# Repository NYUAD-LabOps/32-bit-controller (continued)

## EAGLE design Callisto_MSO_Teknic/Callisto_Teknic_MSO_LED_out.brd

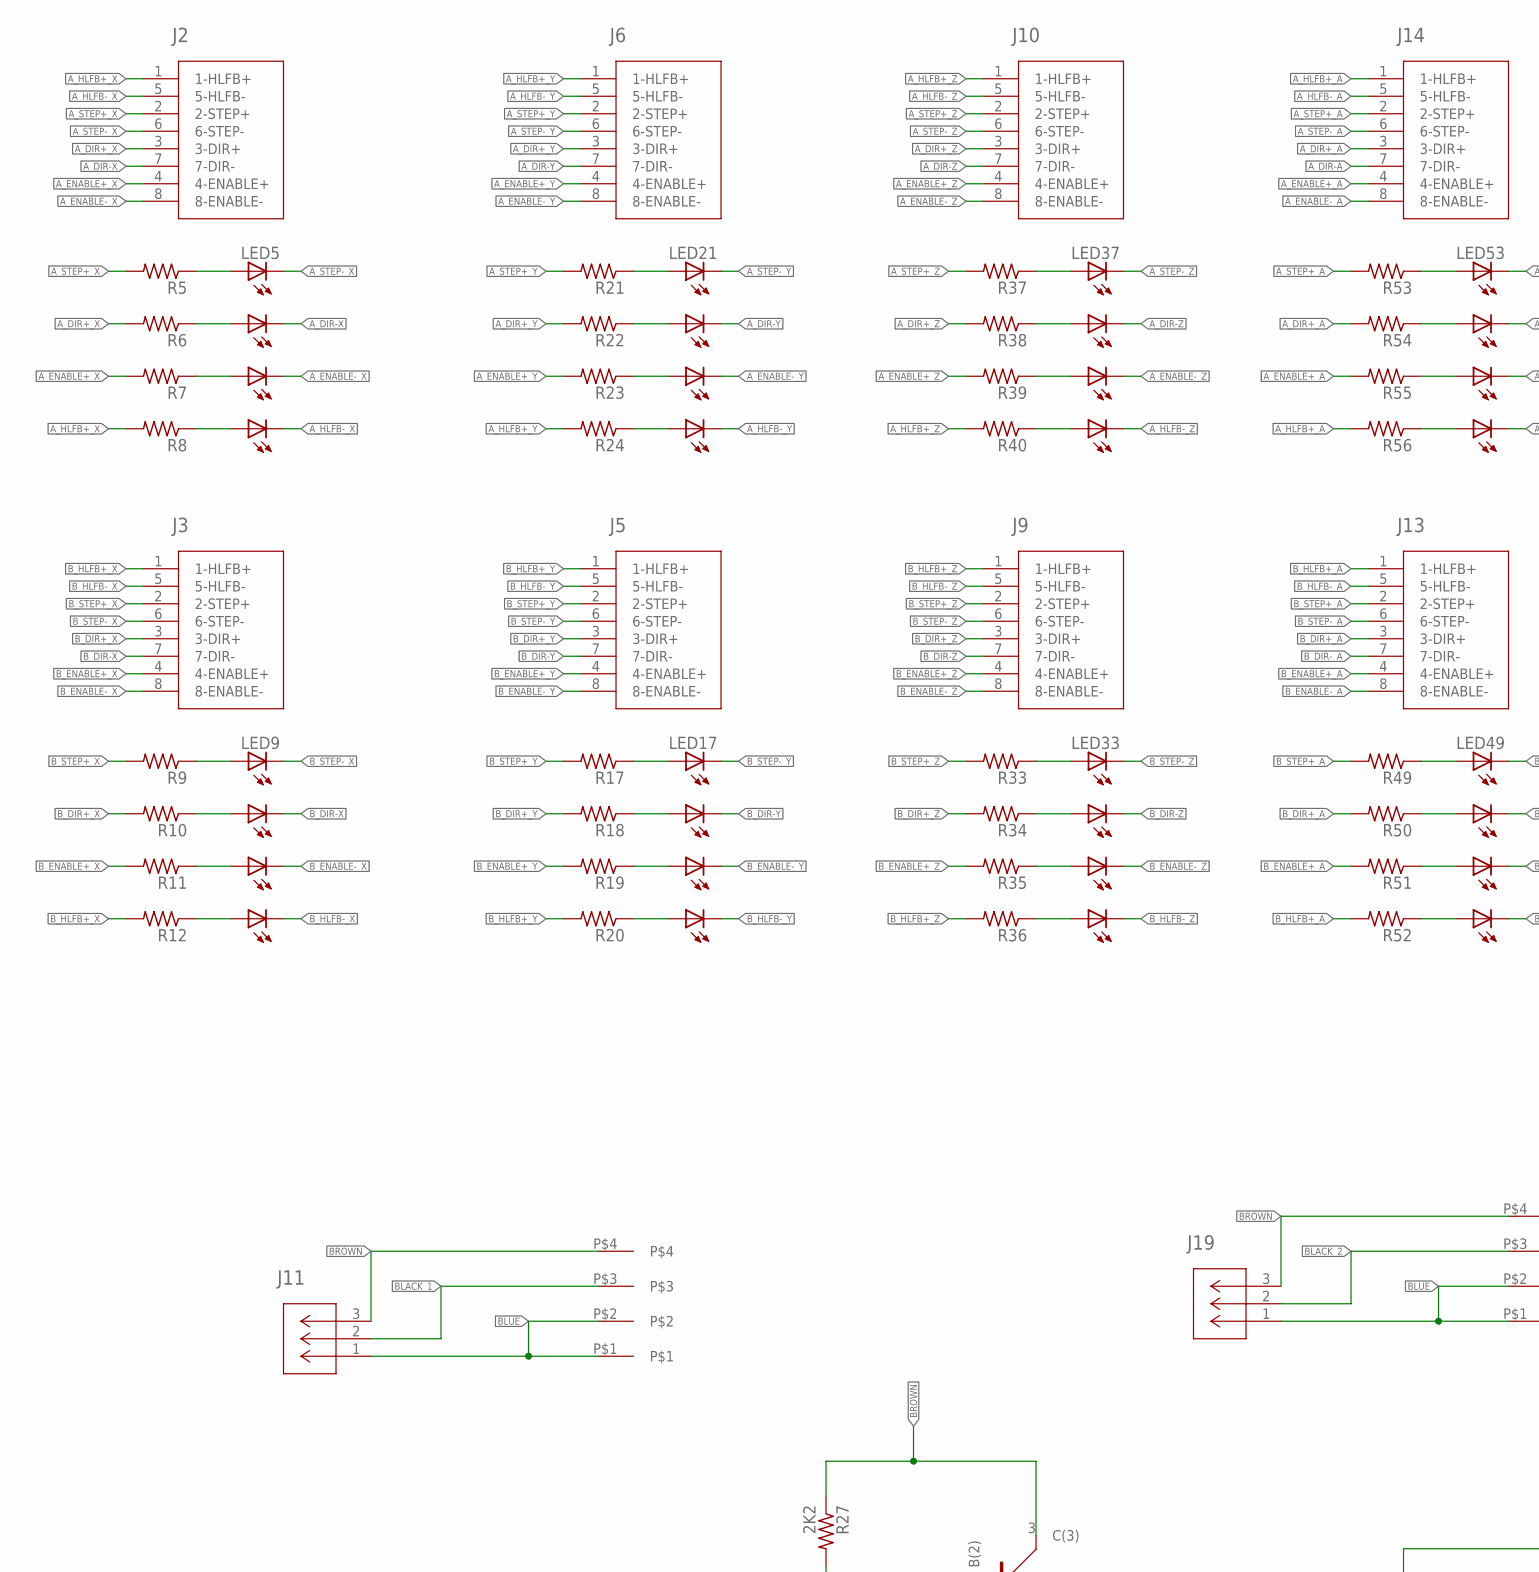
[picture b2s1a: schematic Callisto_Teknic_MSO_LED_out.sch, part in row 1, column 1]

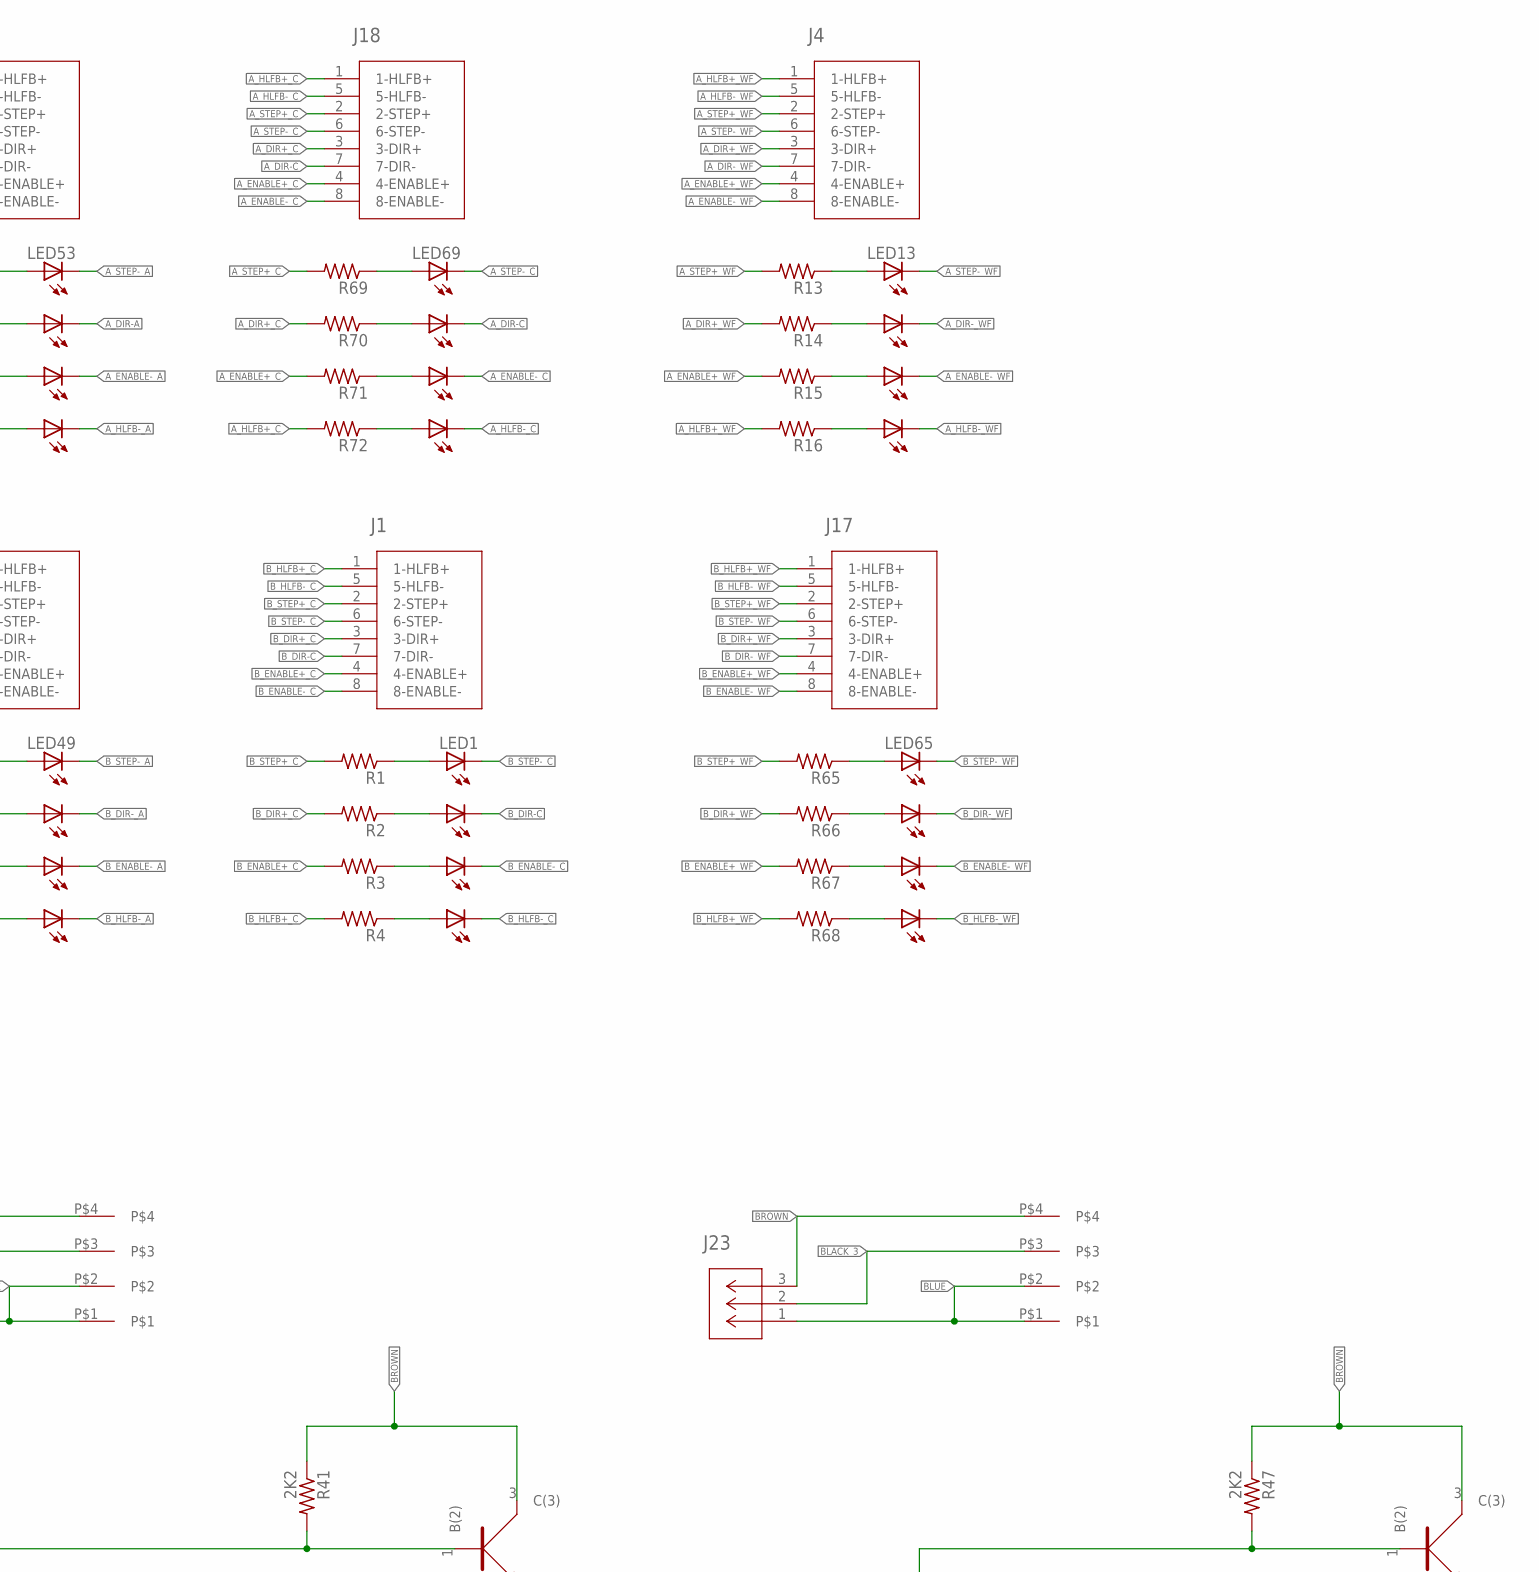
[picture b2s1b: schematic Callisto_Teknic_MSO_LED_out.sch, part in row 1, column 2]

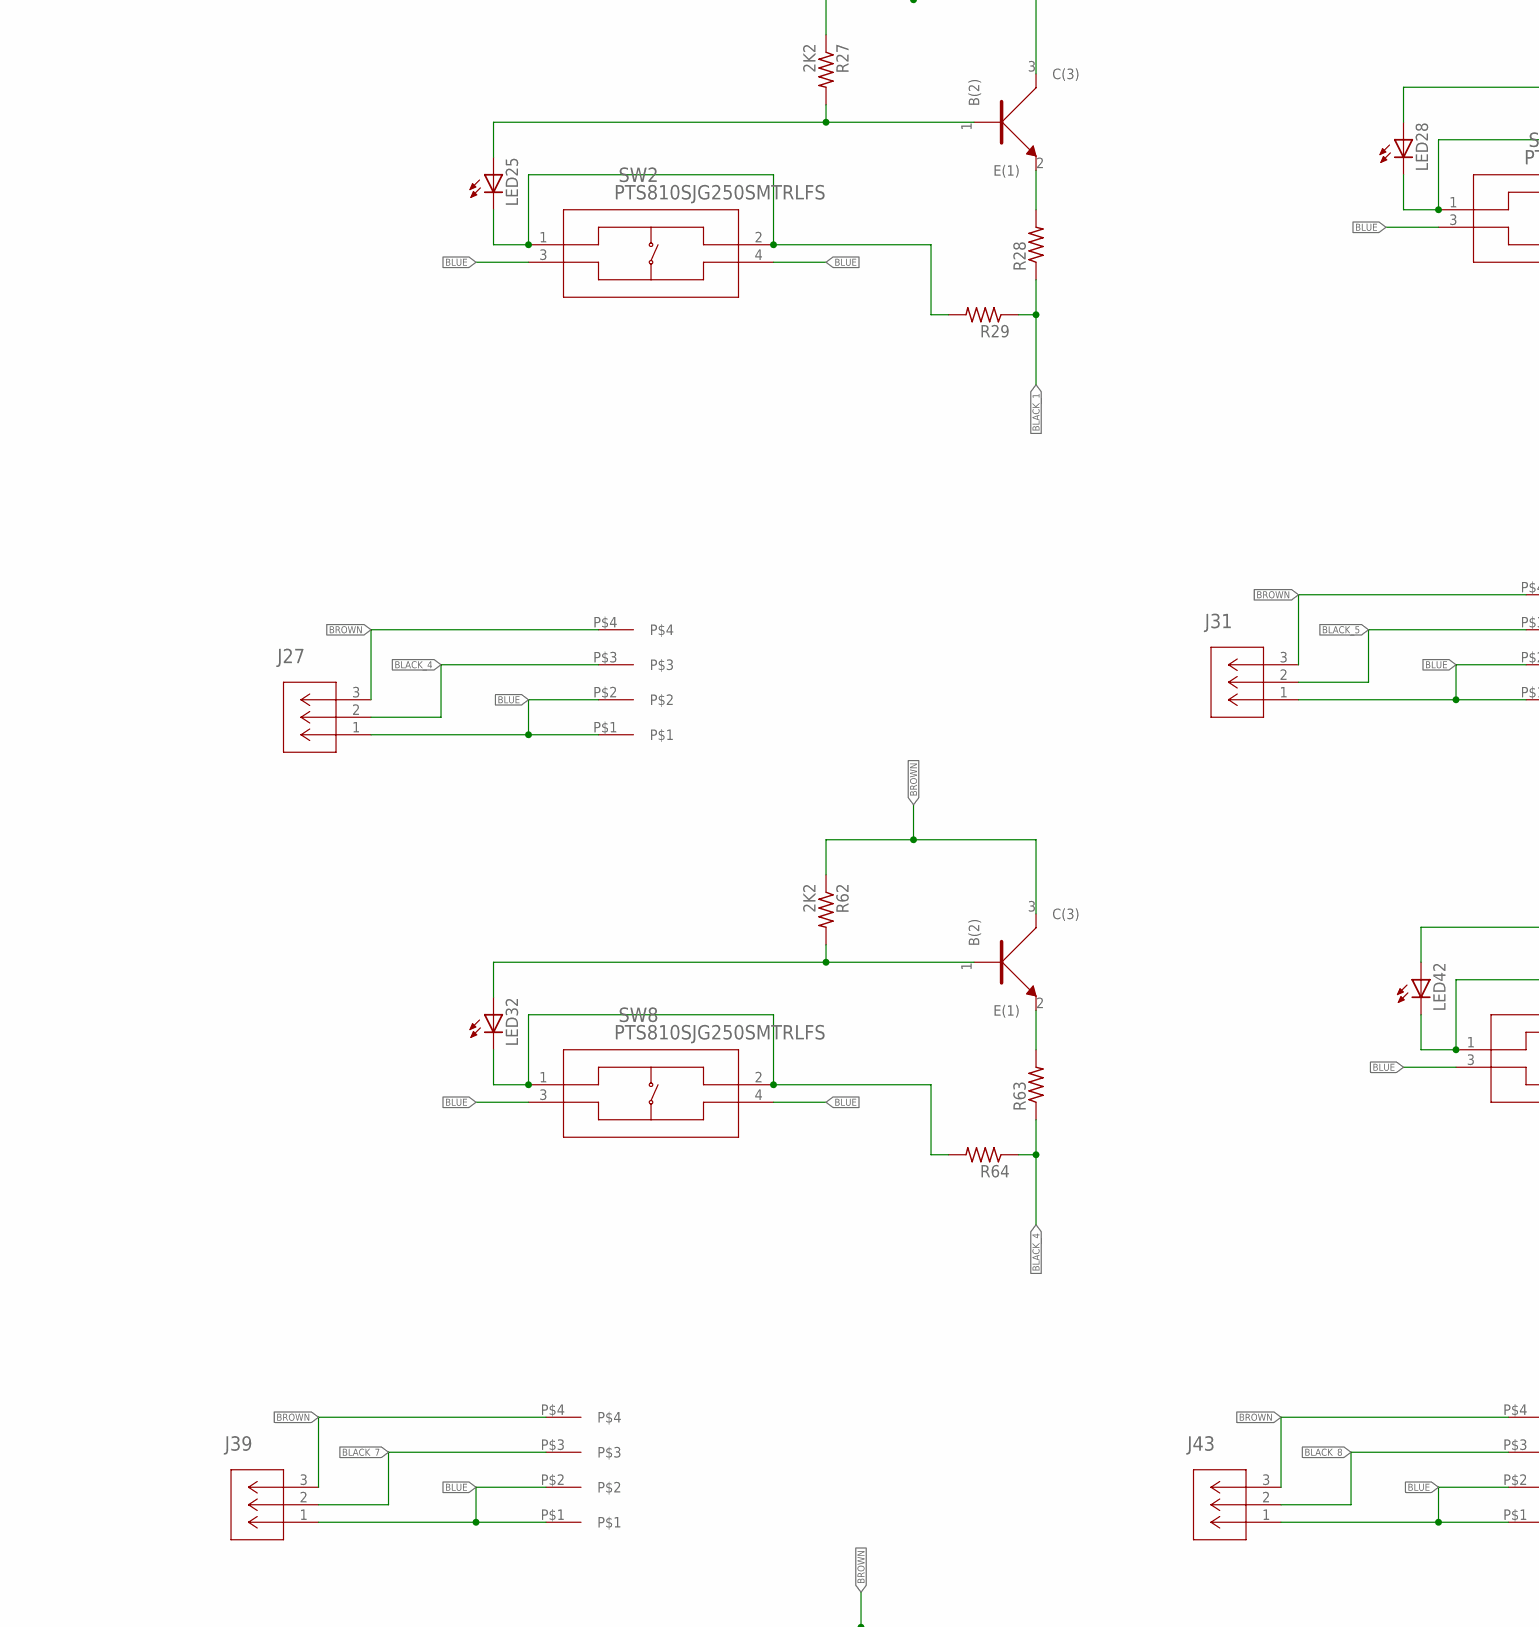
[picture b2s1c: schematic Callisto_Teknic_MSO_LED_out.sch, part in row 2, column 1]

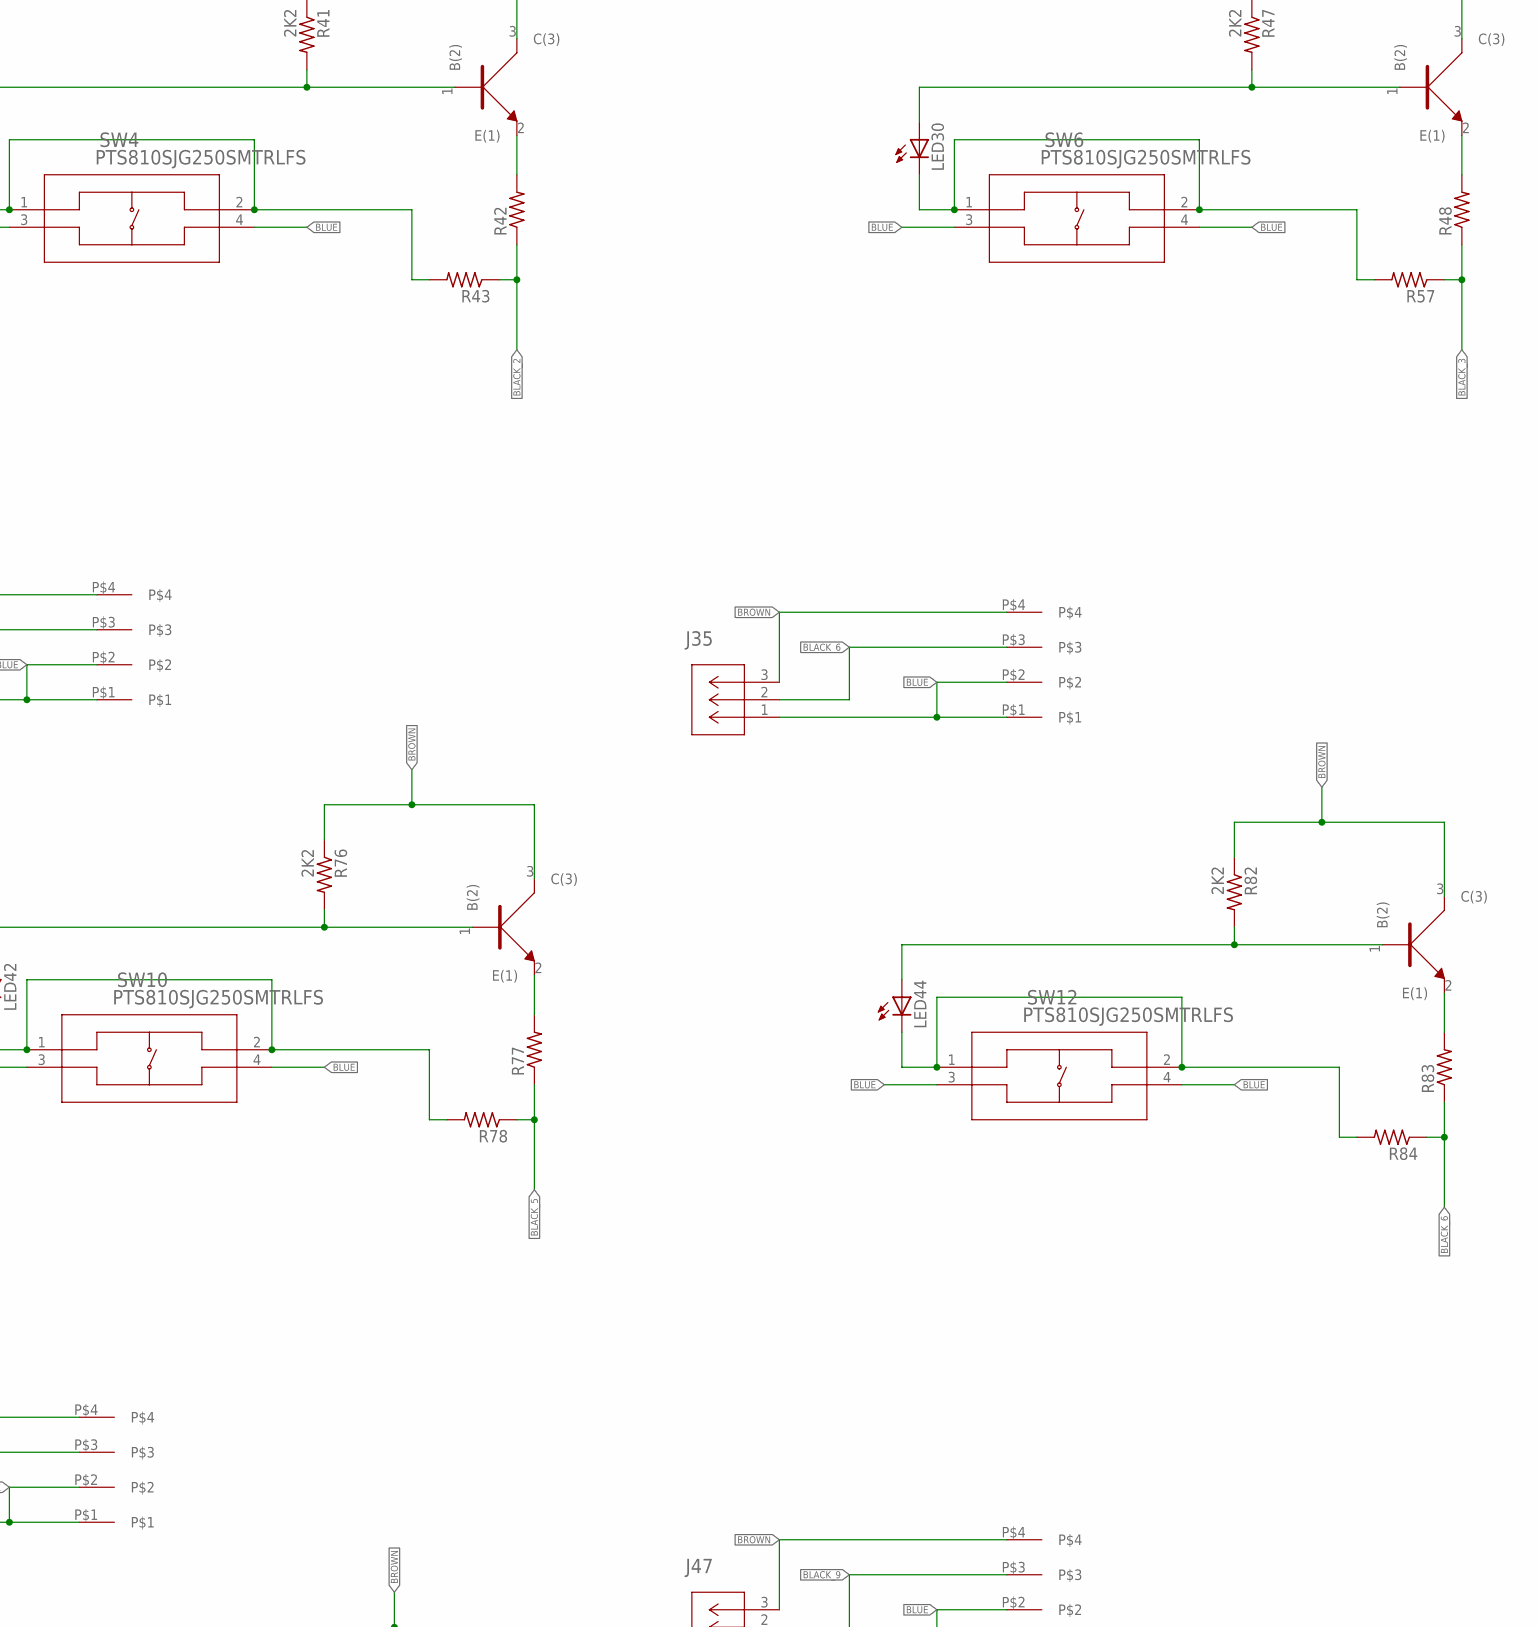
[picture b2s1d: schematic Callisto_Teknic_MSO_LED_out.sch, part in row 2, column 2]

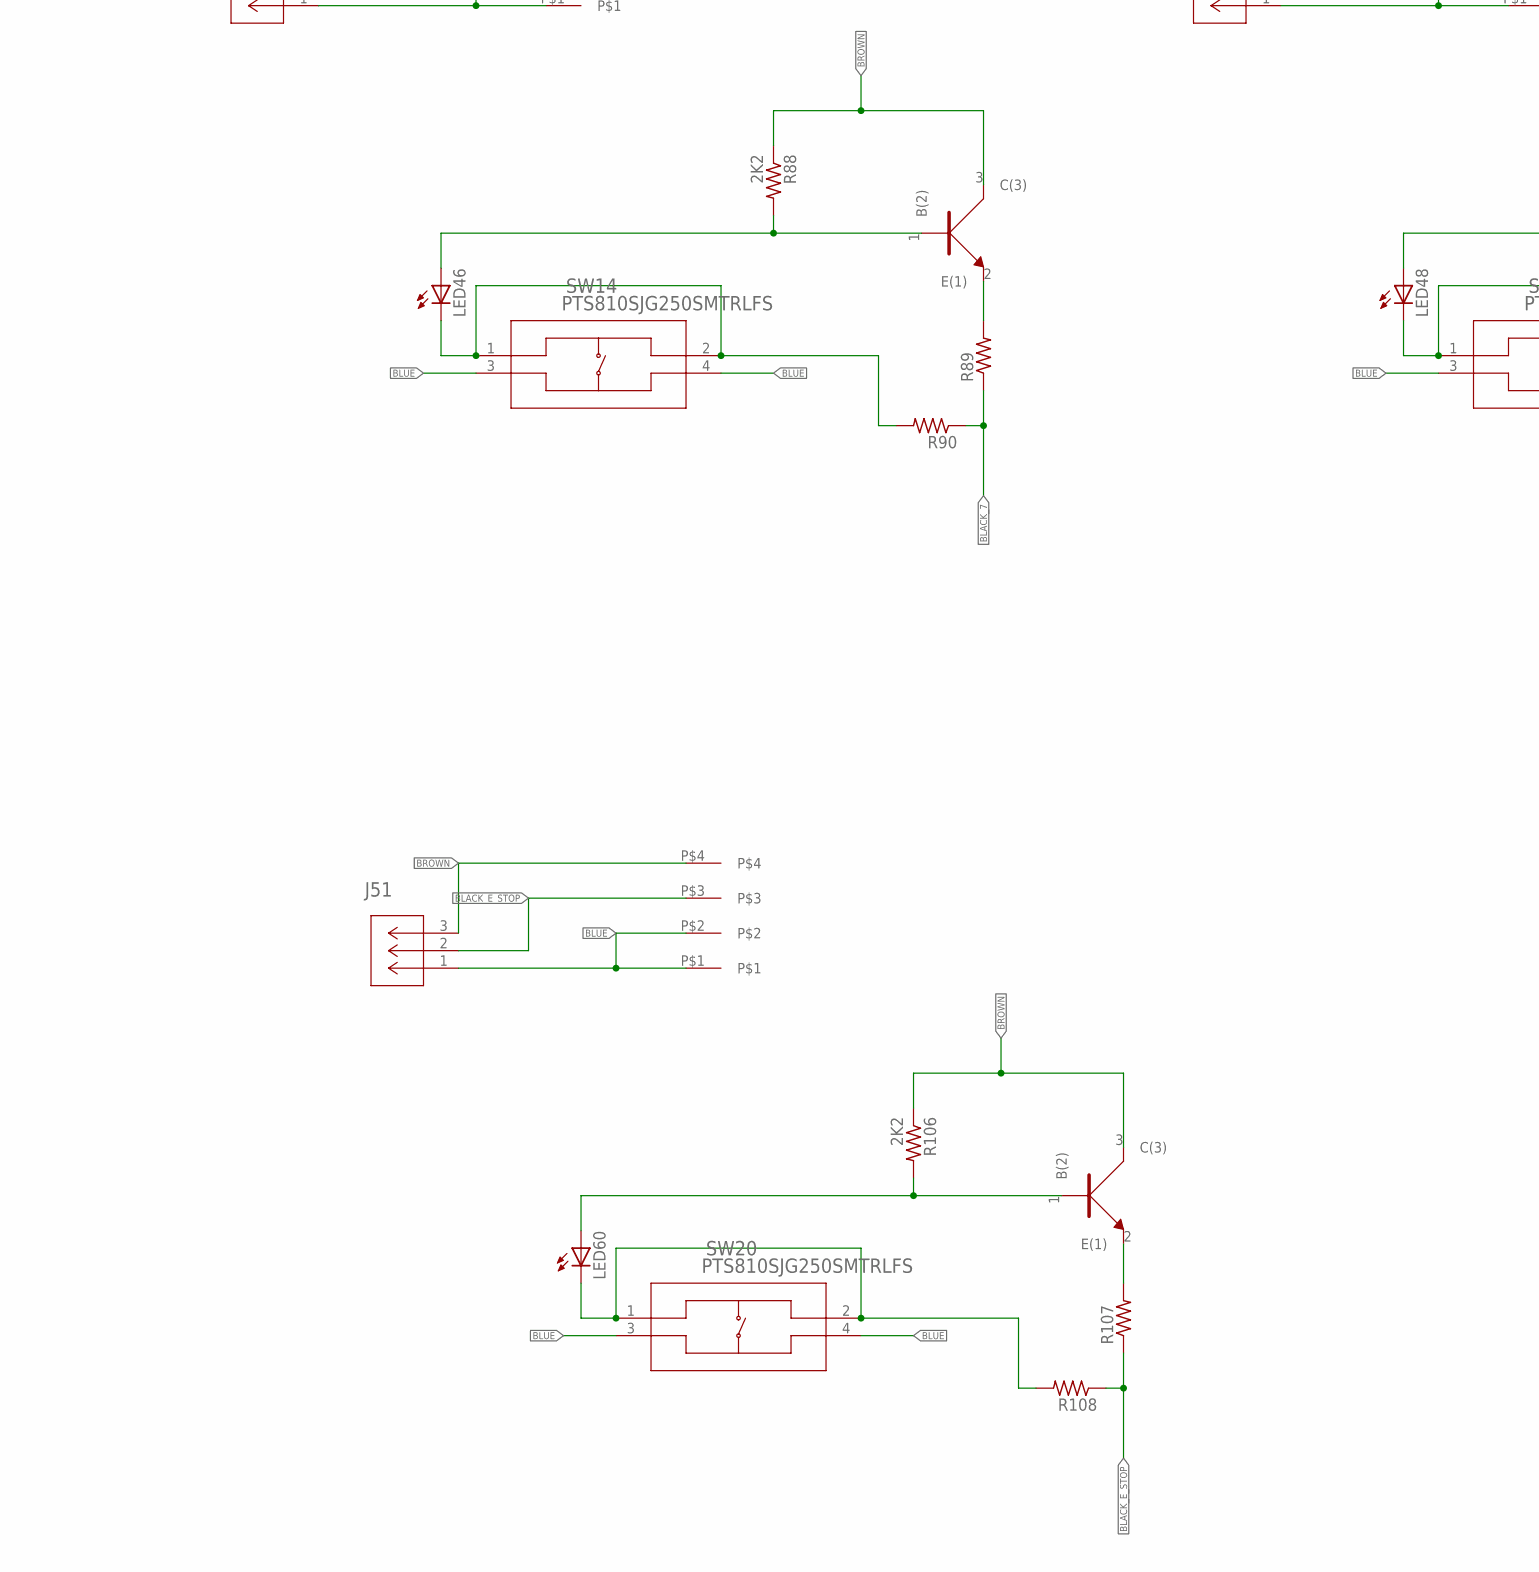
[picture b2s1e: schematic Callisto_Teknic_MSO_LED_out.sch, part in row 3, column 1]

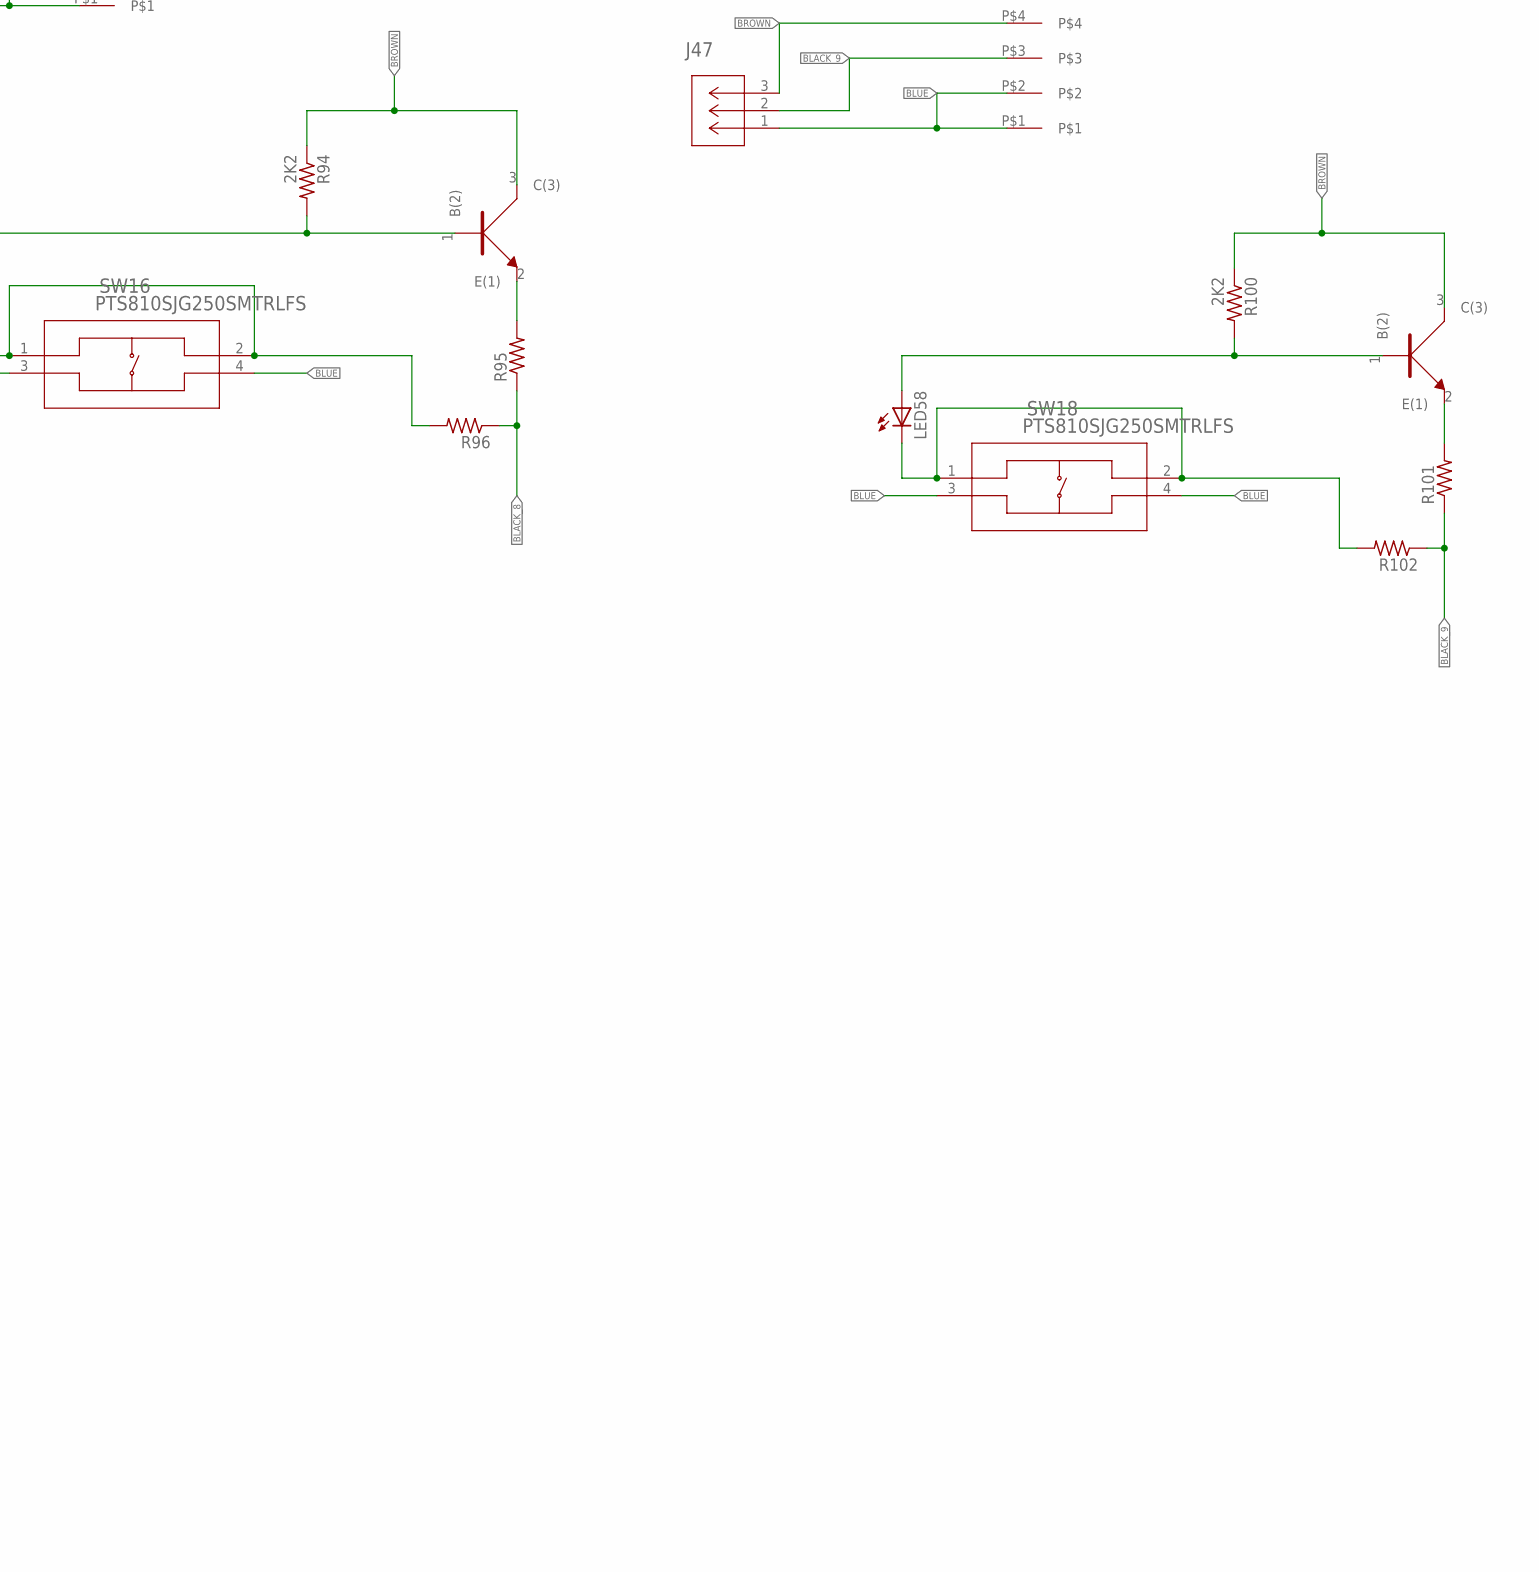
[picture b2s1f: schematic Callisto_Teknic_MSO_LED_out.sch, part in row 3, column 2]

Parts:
J1, J2, J3, J4, J5, J6, J9, J10, J13, J14, J17, J18: TEKNIC_MOTOR_SD_8PIN; CON_39281083
J11, J19, J23, J27, J31, J35, J39, J43, J47, J51: CONN_530470310_PICOBLADE_X_3; CON_530470310_MOL
J12, J20, J24, J28, J32, J36, J40, J44, J48, J52: 4-pos; 1X4_3.81MM_PITCH
LED1, LED2, LED3, LED4, LED5, LED6, LED7, LED8, LED9, LED10, LED11, LED12, LED13, LED14, LED15, LED16, LED17, LED18, LED19, LED20, LED21, LED22, LED23, LED24, LED25, LED28, LED30, LED32, LED33, LED34, LED35, LED36, LED37, LED38, LED39, LED40, LED42, LED44, LED46, LED48, LED49, LED50, LED51, LED52, LED53, LED54, LED55, LED56, LED58, LED60, LED65, LED66, LED67, LED68, LED69, LED70, LED71, LED72: Green; 0805
R1, R2, R3, R4, R5, R6, R7, R8, R9, R10, R11, R12, R13, R14, R15, R16, R17, R18, R19, R20, R21, R22, R23, R24, R33, R34, R35, R36, R37, R38, R39, R40, R49, R50, R51, R52, R53, R54, R55, R56, R65, R66, R67, R68, R69, R70, R71, R72: R_0805; 0805
R27, R41, R47, R62, R76, R82, R88, R94, R100, R106: 2K2; 0402
R28, R29, R42, R43, R48, R57, R63, R64, R77, R78, R83, R84, R89, R90, R95, R96, R101, R102, R107, R108: R_0402; 0402
SW2, SW4, SW6, SW8, SW10, SW12, SW14, SW16, SW18, SW20: PTS810SJG250SMTRLFS; PTS810
U1, U3, U5, U7, U9, U11, U13, U15, U17, U20: NPN; SOT323

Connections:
A_DIR+_A: J14.3 (3-DIR+), R54.2
A_DIR+_C: J18.3 (3-DIR+), R70.2
A_DIR+_WF: J4.3 (3-DIR+), R14.2
A_DIR+_X: J2.3 (3-DIR+), R6.2
A_DIR+_Y: J6.3 (3-DIR+), R22.2
A_DIR+_Z: J10.3 (3-DIR+), R38.2
A_DIR-A: J14.7 (7-DIR-), LED54.2 (C)
A_DIR-C: J18.7 (7-DIR-), LED70.2 (C)
A_DIR-X: J2.7 (7-DIR-), LED6.2 (C)
A_DIR-Y: J6.7 (7-DIR-), LED22.2 (C)
A_DIR-Z: J10.7 (7-DIR-), LED38.2 (C)
A_DIR-_WF: J4.7 (7-DIR-), LED14.2 (C)
A_ENABLE+_A: J14.4 (4-ENABLE+), R55.2
A_ENABLE+_C: J18.4 (4-ENABLE+), R71.2
A_ENABLE+_WF: J4.4 (4-ENABLE+), R15.2
A_ENABLE+_X: J2.4 (4-ENABLE+), R7.2
A_ENABLE+_Y: J6.4 (4-ENABLE+), R23.2
A_ENABLE+_Z: J10.4 (4-ENABLE+), R39.2
A_ENABLE-_A: J14.8 (8-ENABLE-), LED55.2 (C)
A_ENABLE-_C: J18.8 (8-ENABLE-), LED71.2 (C)
A_ENABLE-_WF: J4.8 (8-ENABLE-), LED15.2 (C)
A_ENABLE-_X: J2.8 (8-ENABLE-), LED7.2 (C)
A_ENABLE-_Y: J6.8 (8-ENABLE-), LED23.2 (C)
A_ENABLE-_Z: J10.8 (8-ENABLE-), LED39.2 (C)
A_HLFB+_A: J14.1 (1-HLFB+), R56.2
A_HLFB+_C: J18.1 (1-HLFB+), R72.2
A_HLFB+_WF: J4.1 (1-HLFB+), R16.2
A_HLFB+_X: J2.1 (1-HLFB+), R8.2
A_HLFB+_Y: J6.1 (1-HLFB+), R24.2
A_HLFB+_Z: J10.1 (1-HLFB+), R40.2
A_HLFB-_A: J14.5 (5-HLFB-), LED56.2 (C)
A_HLFB-_C: J18.5 (5-HLFB-), LED72.2 (C)
A_HLFB-_WF: J4.5 (5-HLFB-), LED16.2 (C)
A_HLFB-_X: J2.5 (5-HLFB-), LED8.2 (C)
A_HLFB-_Y: J6.5 (5-HLFB-), LED24.2 (C)
A_HLFB-_Z: J10.5 (5-HLFB-), LED40.2 (C)
A_STEP+_A: J14.2 (2-STEP+), R53.2
A_STEP+_C: J18.2 (2-STEP+), R69.2
A_STEP+_WF: J4.2 (2-STEP+), R13.2
A_STEP+_X: J2.2 (2-STEP+), R5.2
A_STEP+_Y: J6.2 (2-STEP+), R21.2
A_STEP+_Z: J10.2 (2-STEP+), R37.2
A_STEP-_A: J14.6 (6-STEP-), LED53.2 (C)
A_STEP-_C: J18.6 (6-STEP-), LED69.2 (C)
A_STEP-_WF: J4.6 (6-STEP-), LED13.2 (C)
A_STEP-_X: J2.6 (6-STEP-), LED5.2 (C)
A_STEP-_Y: J6.6 (6-STEP-), LED21.2 (C)
A_STEP-_Z: J10.6 (6-STEP-), LED37.2 (C)
BLACK_1: J11.2, J12.P$3, R28.P$1 (1), R29.P$1 (1)
BLACK_2: J19.2, J20.P$3, R42.P$1 (1), R43.P$1 (1)
BLACK_3: J23.2, J24.P$3, R48.P$1 (1), R57.P$1 (1)
BLACK_4: J27.2, J28.P$3, R63.P$1 (1), R64.P$1 (1)
BLACK_5: J31.2, J32.P$3, R77.P$1 (1), R78.P$1 (1)
BLACK_6: J35.2, J36.P$3, R83.P$1 (1), R84.P$1 (1)
BLACK_7: J39.2, J40.P$3, R89.P$1 (1), R90.P$1 (1)
BLACK_8: J43.2, J44.P$3, R95.P$1 (1), R96.P$1 (1)
BLACK_9: J47.2, J48.P$3, R101.P$1 (1), R102.P$1 (1)
BLACK_E_STOP: J51.2, J52.P$3, R107.P$1 (1), R108.P$1 (1)
BLUE: J11.1, J12.P$1, J12.P$2, J19.1, J20.P$1, J20.P$2, J23.1, J24.P$1, J24.P$2, J27.1, J28.P$1, J28.P$2, J31.1, J32.P$1, J32.P$2, J35.1, J36.P$1, J36.P$2, J39.1, J40.P$1, J40.P$2, J43.1, J44.P$1, J44.P$2, J47.1, J48.P$1, J48.P$2, J51.1, J52.P$1, J52.P$2, SW2.3, SW2.4, SW4.3, SW4.4, SW6.3, SW6.4, SW8.3, SW8.4, SW10.3, SW10.4, SW12.3, SW12.4, SW14.3, SW14.4, SW16.3, SW16.4, SW18.3, SW18.4, SW20.3, SW20.4
BROWN: J11.3, J12.P$4, J19.3, J20.P$4, J23.3, J24.P$4, J27.3, J28.P$4, J31.3, J32.P$4, J35.3, J36.P$4, J39.3, J40.P$4, J43.3, J44.P$4, J47.3, J48.P$4, J51.3, J52.P$4, R27.P$1 (1), R41.P$1 (1), R47.P$1 (1), R62.P$1 (1), R76.P$1 (1), R82.P$1 (1), R88.P$1 (1), R94.P$1 (1), R100.P$1 (1), R106.P$1 (1), U1.3 (C(3)), U3.3 (C(3)), U5.3 (C(3)), U7.3 (C(3)), U9.3 (C(3)), U11.3 (C(3)), U13.3 (C(3)), U15.3 (C(3)), U17.3 (C(3)), U20.3 (C(3))
B_DIR+_A: J13.3 (3-DIR+), R50.2
B_DIR+_C: J1.3 (3-DIR+), R2.2
B_DIR+_WF: J17.3 (3-DIR+), R66.2
B_DIR+_X: J3.3 (3-DIR+), R10.2
B_DIR+_Y: J5.3 (3-DIR+), R18.2
B_DIR+_Z: J9.3 (3-DIR+), R34.2
B_DIR-C: J1.7 (7-DIR-), LED2.2 (C)
B_DIR-X: J3.7 (7-DIR-), LED10.2 (C)
B_DIR-Y: J5.7 (7-DIR-), LED18.2 (C)
B_DIR-Z: J9.7 (7-DIR-), LED34.2 (C)
B_DIR-_A: J13.7 (7-DIR-), LED50.2 (C)
B_DIR-_WF: J17.7 (7-DIR-), LED66.2 (C)
B_ENABLE+_A: J13.4 (4-ENABLE+), R51.2
B_ENABLE+_C: J1.4 (4-ENABLE+), R3.2
B_ENABLE+_WF: J17.4 (4-ENABLE+), R67.2
B_ENABLE+_X: J3.4 (4-ENABLE+), R11.2
B_ENABLE+_Y: J5.4 (4-ENABLE+), R19.2
B_ENABLE+_Z: J9.4 (4-ENABLE+), R35.2
B_ENABLE-_A: J13.8 (8-ENABLE-), LED51.2 (C)
B_ENABLE-_C: J1.8 (8-ENABLE-), LED3.2 (C)
B_ENABLE-_WF: J17.8 (8-ENABLE-), LED67.2 (C)
B_ENABLE-_X: J3.8 (8-ENABLE-), LED11.2 (C)
B_ENABLE-_Y: J5.8 (8-ENABLE-), LED19.2 (C)
B_ENABLE-_Z: J9.8 (8-ENABLE-), LED35.2 (C)
B_HLFB+_A: J13.1 (1-HLFB+), R52.2
B_HLFB+_C: J1.1 (1-HLFB+), R4.2
B_HLFB+_WF: J17.1 (1-HLFB+), R68.2
B_HLFB+_X: J3.1 (1-HLFB+), R12.2
B_HLFB+_Y: J5.1 (1-HLFB+), R20.2
B_HLFB+_Z: J9.1 (1-HLFB+), R36.2
B_HLFB-_A: J13.5 (5-HLFB-), LED52.2 (C)
B_HLFB-_C: J1.5 (5-HLFB-), LED4.2 (C)
B_HLFB-_WF: J17.5 (5-HLFB-), LED68.2 (C)
B_HLFB-_X: J3.5 (5-HLFB-), LED12.2 (C)
B_HLFB-_Y: J5.5 (5-HLFB-), LED20.2 (C)
B_HLFB-_Z: J9.5 (5-HLFB-), LED36.2 (C)
B_STEP+_A: J13.2 (2-STEP+), R49.2
B_STEP+_C: J1.2 (2-STEP+), R1.2
B_STEP+_WF: J17.2 (2-STEP+), R65.2
B_STEP+_X: J3.2 (2-STEP+), R9.2
B_STEP+_Y: J5.2 (2-STEP+), R17.2
B_STEP+_Z: J9.2 (2-STEP+), R33.2
B_STEP-_A: J13.6 (6-STEP-), LED49.2 (C)
B_STEP-_C: J1.6 (6-STEP-), LED1.2 (C)
B_STEP-_WF: J17.6 (6-STEP-), LED65.2 (C)
B_STEP-_X: J3.6 (6-STEP-), LED9.2 (C)
B_STEP-_Y: J5.6 (6-STEP-), LED17.2 (C)
B_STEP-_Z: J9.6 (6-STEP-), LED33.2 (C)
unnamed: LED1.1 (A), R1.1
unnamed: LED2.1 (A), R2.1
unnamed: LED3.1 (A), R3.1
unnamed: LED4.1 (A), R4.1
unnamed: LED5.1 (A), R5.1
unnamed: LED6.1 (A), R6.1
unnamed: LED7.1 (A), R7.1
unnamed: LED8.1 (A), R8.1
unnamed: LED9.1 (A), R9.1
unnamed: LED10.1 (A), R10.1
unnamed: LED11.1 (A), R11.1
unnamed: LED12.1 (A), R12.1
unnamed: LED13.1 (A), R13.1
unnamed: LED14.1 (A), R14.1
unnamed: LED15.1 (A), R15.1
unnamed: LED16.1 (A), R16.1
unnamed: LED17.1 (A), R17.1
unnamed: LED18.1 (A), R18.1
unnamed: LED19.1 (A), R19.1
unnamed: LED20.1 (A), R20.1
unnamed: LED21.1 (A), R21.1
unnamed: LED22.1 (A), R22.1
unnamed: LED23.1 (A), R23.1
unnamed: LED24.1 (A), R24.1
unnamed: LED25.1 (A), R27.P$2 (2), U1.1 (B(2))
unnamed: LED25.2 (C), R29.P$2 (2), SW2.1, SW2.2
unnamed: R28.P$2 (2), U1.2 (E(1))
unnamed: LED33.1 (A), R33.1
unnamed: LED34.1 (A), R34.1
unnamed: LED35.1 (A), R35.1
unnamed: LED36.1 (A), R36.1
unnamed: LED37.1 (A), R37.1
unnamed: LED38.1 (A), R38.1
unnamed: LED39.1 (A), R39.1
unnamed: LED40.1 (A), R40.1
unnamed: LED28.1 (A), R41.P$2 (2), U3.1 (B(2))
unnamed: LED28.2 (C), R43.P$2 (2), SW4.1, SW4.2
unnamed: R42.P$2 (2), U3.2 (E(1))
unnamed: LED30.1 (A), R47.P$2 (2), U5.1 (B(2))
unnamed: LED49.1 (A), R49.1
unnamed: LED50.1 (A), R50.1
unnamed: LED51.1 (A), R51.1
unnamed: LED52.1 (A), R52.1
unnamed: LED53.1 (A), R53.1
unnamed: LED54.1 (A), R54.1
unnamed: LED55.1 (A), R55.1
unnamed: LED56.1 (A), R56.1
unnamed: LED30.2 (C), R57.P$2 (2), SW6.1, SW6.2
unnamed: R48.P$2 (2), U5.2 (E(1))
unnamed: LED32.1 (A), R62.P$2 (2), U7.1 (B(2))
unnamed: LED32.2 (C), R64.P$2 (2), SW8.1, SW8.2
unnamed: R63.P$2 (2), U7.2 (E(1))
unnamed: LED65.1 (A), R65.1
unnamed: LED66.1 (A), R66.1
unnamed: LED67.1 (A), R67.1
unnamed: LED68.1 (A), R68.1
unnamed: LED69.1 (A), R69.1
unnamed: LED70.1 (A), R70.1
unnamed: LED71.1 (A), R71.1
unnamed: LED72.1 (A), R72.1
unnamed: LED42.1 (A), R76.P$2 (2), U9.1 (B(2))
unnamed: LED42.2 (C), R78.P$2 (2), SW10.1, SW10.2
unnamed: R77.P$2 (2), U9.2 (E(1))
unnamed: LED44.1 (A), R82.P$2 (2), U11.1 (B(2))
unnamed: LED44.2 (C), R84.P$2 (2), SW12.1, SW12.2
unnamed: R83.P$2 (2), U11.2 (E(1))
unnamed: LED46.1 (A), R88.P$2 (2), U13.1 (B(2))
unnamed: LED46.2 (C), R90.P$2 (2), SW14.1, SW14.2
unnamed: R89.P$2 (2), U13.2 (E(1))
unnamed: LED48.1 (A), R94.P$2 (2), U15.1 (B(2))
unnamed: LED48.2 (C), R96.P$2 (2), SW16.1, SW16.2
unnamed: R95.P$2 (2), U15.2 (E(1))
unnamed: LED58.1 (A), R100.P$2 (2), U17.1 (B(2))
unnamed: LED58.2 (C), R102.P$2 (2), SW18.1, SW18.2
unnamed: R101.P$2 (2), U17.2 (E(1))
unnamed: LED60.1 (A), R106.P$2 (2), U20.1 (B(2))
unnamed: LED60.2 (C), R108.P$2 (2), SW20.1, SW20.2
unnamed: R107.P$2 (2), U20.2 (E(1))

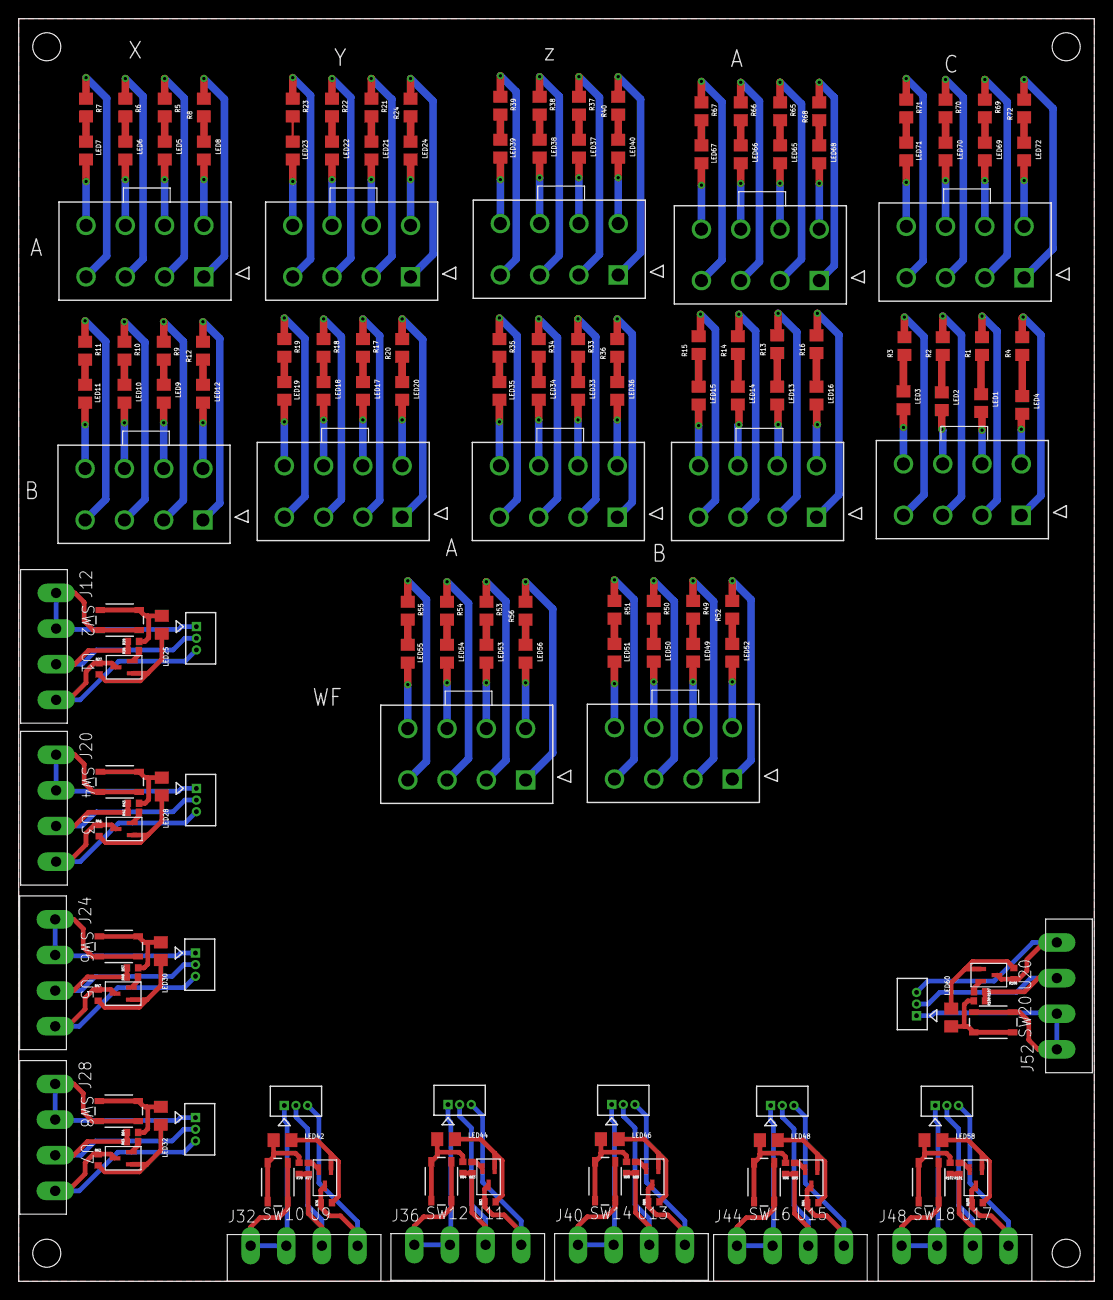
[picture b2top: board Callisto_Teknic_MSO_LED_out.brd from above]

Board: 2 copper layers, 115.0 x 135.0 mm, 188 parts (0 on the bottom side), 186 nets.
